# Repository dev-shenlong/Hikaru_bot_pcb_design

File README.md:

# Hikaru_bot_pcb_design
This is a repo consisting of KiCAD design files for the autonomous Differential Drive Robot

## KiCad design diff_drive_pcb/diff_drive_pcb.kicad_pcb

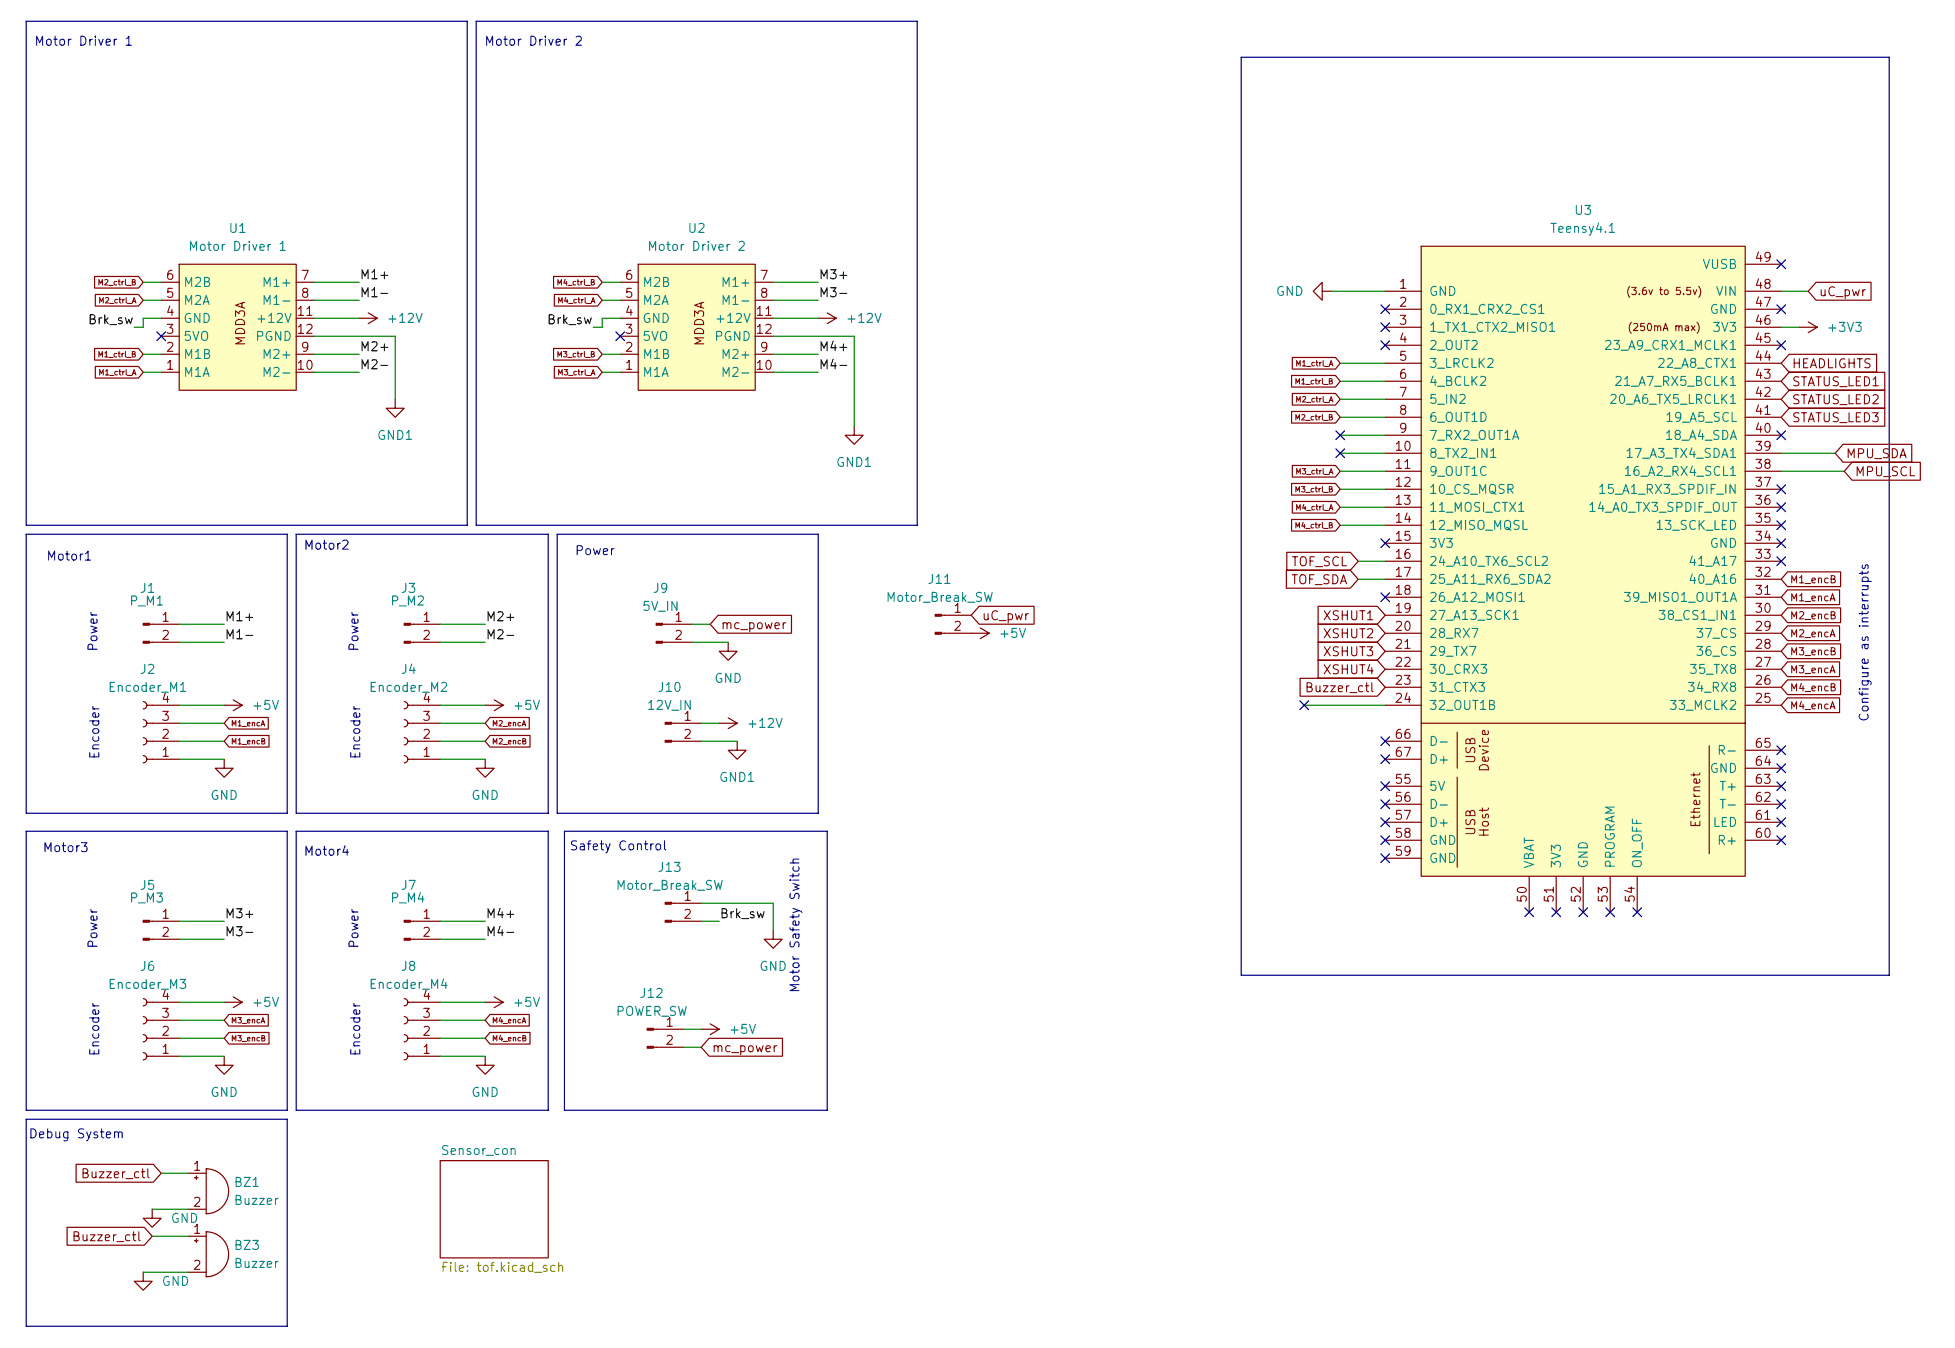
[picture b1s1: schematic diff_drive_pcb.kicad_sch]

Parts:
BZ1, BZ3: Buzzer; Buzzer_TDK_PS1240P02BT_D12.2mm_H6.5mm
J1: P_M1; JST_XH_B2B-XH-A_1x02_P2.50mm_Vertical
J2: Encoder_M1; JST_XH_B4B-XH-A_1x04_P2.50mm_Vertical
J3: P_M2; JST_XH_B2B-XH-A_1x02_P2.50mm_Vertical
J4: Encoder_M2; JST_XH_B4B-XH-A_1x04_P2.50mm_Vertical
J5: P_M3; JST_XH_B2B-XH-A_1x02_P2.50mm_Vertical
J6: Encoder_M3; JST_XH_B4B-XH-A_1x04_P2.50mm_Vertical
J7: P_M4; JST_XH_B2B-XH-A_1x02_P2.50mm_Vertical
J8: Encoder_M4; JST_XH_B4B-XH-A_1x04_P2.50mm_Vertical
J9: 5V_IN; JST_XH_B2B-XH-A_1x02_P2.50mm_Vertical
J10: 12V_IN; JST_XH_B2B-XH-A_1x02_P2.50mm_Vertical
J11, J13: Motor_Break_SW; PinHeader_1x02_P2.54mm_Vertical
J12: POWER_SW; JST_XH_B2B-XH-A_1x02_P2.50mm_Vertical
U1: Motor Driver 1; MDD3A
U2: Motor Driver 2; MDD3A
U3: Teensy4.1; Teensy41

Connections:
+3V3: U3.46 (3V3)
+5V: J2.4, J4.4, J6.4, J8.4, J11.2, J12.1; also elsewhere on the board
+12V: J10.1, U1.11 (+12V), U2.11 (+12V)
/Brk_sw: J13.2, U1.4 (GND), U2.4 (GND)
/M1+: J1.1, U1.7 (M1+)
/M1-: J1.2, U1.8 (M1-)
/M2+: J3.1, U1.9 (M2+)
/M2-: J3.2, U1.10 (M2-)
/M3+: J5.1, U2.7 (M1+)
/M3-: J5.2, U2.8 (M1-)
/M4+: J7.1, U2.9 (M2+)
/M4-: J7.2, U2.10 (M2-)
Buzzer_ctl: BZ1.1 (+), BZ3.1 (+), U3.23 (31_CTX3)
GND: BZ1.2 (-), BZ3.2 (-), J2.1, J4.1, J6.1, J8.1, J9.2, J13.1, U3.1 (GND); also elsewhere on the board
GND1: J10.2, U1.12 (PGND), U2.12 (PGND)
HEADLIGHTS: U3.44 (22_A8_CTX1); also elsewhere on the board
M1_ctrl_A: U1.1 (M1A), U3.5 (3_LRCLK2)
M1_ctrl_B: U1.2 (M1B), U3.6 (4_BCLK2)
M1_encA: J2.3, U3.31 (39_MISO1_OUT1A)
M1_encB: J2.2, U3.32 (40_A16)
M2_ctrl_A: U1.5 (M2A), U3.7 (5_IN2)
M2_ctrl_B: U1.6 (M2B), U3.8 (6_OUT1D)
M2_encA: J4.3, U3.29 (37_CS)
M2_encB: J4.2, U3.30 (38_CS1_IN1)
M3_ctrl_A: U2.1 (M1A), U3.11 (9_OUT1C)
M3_ctrl_B: U2.2 (M1B), U3.12 (10_CS_MQSR)
M3_encA: J6.3, U3.27 (35_TX8)
M3_encB: J6.2, U3.28 (36_CS)
M4_ctrl_A: U2.5 (M2A), U3.13 (11_MOSI_CTX1)
M4_ctrl_B: U2.6 (M2B), U3.14 (12_MISO_MQSL)
M4_encA: J8.3, U3.25 (33_MCLK2)
M4_encB: J8.2, U3.26 (34_RX8)
MPU_SCL: U3.38 (16_A2_RX4_SCL1); also elsewhere on the board
MPU_SDA: U3.39 (17_A3_TX4_SDA1); also elsewhere on the board
STATUS_LED1: U3.43 (21_A7_RX5_BCLK1); also elsewhere on the board
STATUS_LED2: U3.42 (20_A6_TX5_LRCLK1); also elsewhere on the board
STATUS_LED3: U3.41 (19_A5_SCL); also elsewhere on the board
TOF_SCL: U3.16 (24_A10_TX6_SCL2); also elsewhere on the board
TOF_SDA: U3.17 (25_A11_RX6_SDA2); also elsewhere on the board
XSHUT1: U3.19 (27_A13_SCK1); also elsewhere on the board
XSHUT2: U3.20 (28_RX7); also elsewhere on the board
XSHUT3: U3.21 (29_TX7); also elsewhere on the board
XSHUT4: U3.22 (30_CRX3); also elsewhere on the board
mc_power: J9.1, J12.2
uC_pwr: J11.1, U3.48 (VIN)

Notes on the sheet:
Encoder
Configure as interrupts
Motor Driver 2
Safety Control
Motor Driver 1
Motor4
Power
Motor3
Debug System
Motor2
Motor1
Motor Safety Switch

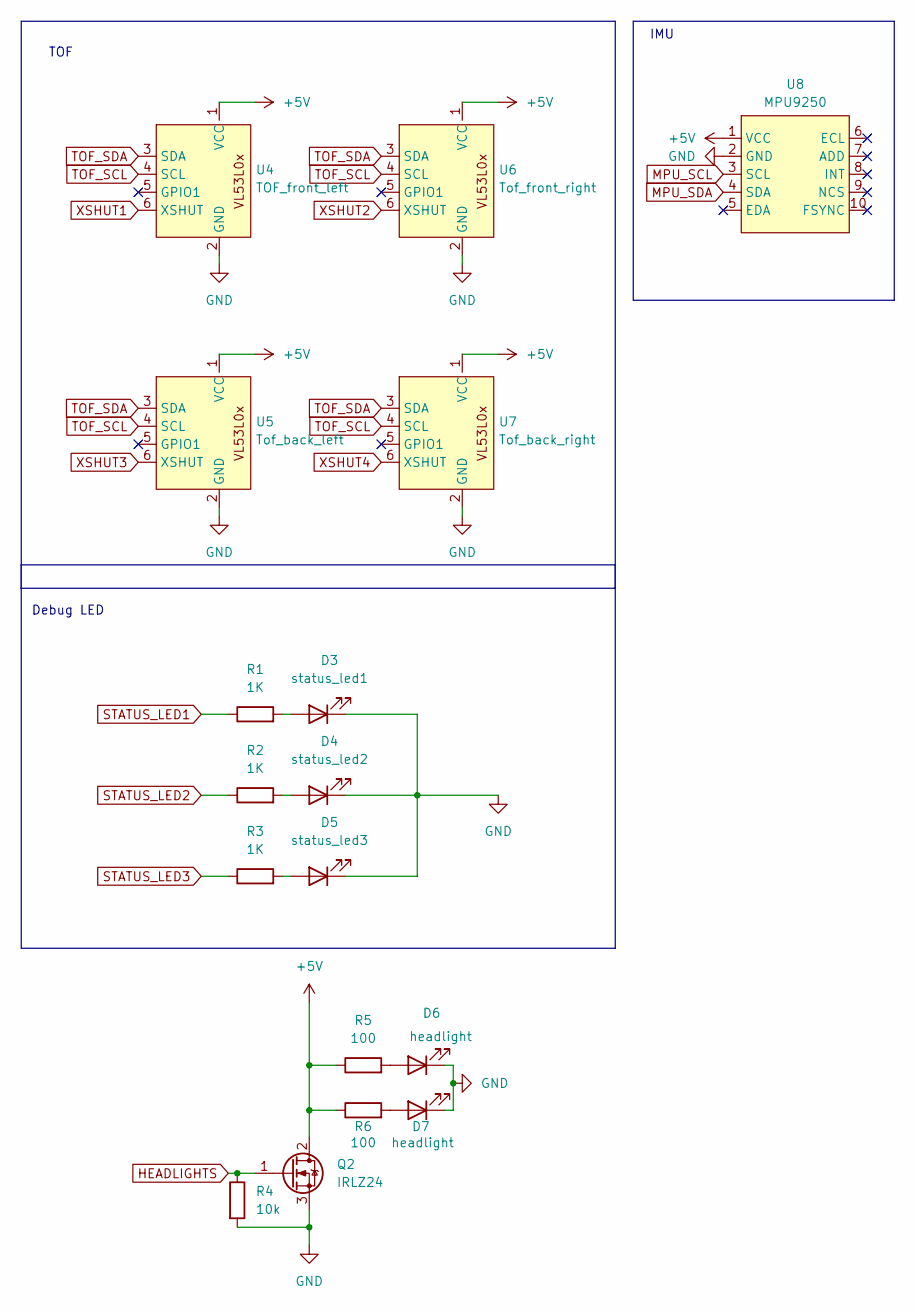
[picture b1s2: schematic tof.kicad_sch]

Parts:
D3: status_led1; PinHeader_1x02_P2.54mm_Vertical
D4: status_led2; PinHeader_1x02_P2.54mm_Vertical
D5: status_led3; PinHeader_1x02_P2.54mm_Vertical
D6, D7: headlight; PinHeader_1x02_P2.54mm_Vertical
Q2: IRLZ24; TO-220-3_Vertical
R1, R2, R3: 1K; R_Axial_DIN0204_L3.6mm_D1.6mm_P2.54mm_Vertical
R4: 10k; R_Axial_DIN0204_L3.6mm_D1.6mm_P5.08mm_Horizontal
R5, R6: 100; R_Axial_DIN0204_L3.6mm_D1.6mm_P5.08mm_Horizontal
U4: TOF_front_left; JST_XH_B6B-XH-A_1x06_P2.50mm_Vertical
U5: Tof_back_left; JST_XH_B6B-XH-A_1x06_P2.50mm_Vertical
U6: Tof_front_right; JST_XH_B6B-XH-A_1x06_P2.50mm_Vertical
U7: Tof_back_right; JST_XH_B6B-XH-A_1x06_P2.50mm_Vertical
U8: MPU9250; PinHeader_1x10_P2.54mm_Vertical

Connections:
+5V: Q2.2 (D), R5.1, R6.1, U4.1 (VCC), U5.1 (VCC), U6.1 (VCC), U7.1 (VCC), U8.1 (VCC); also elsewhere on the board
GND: D3.1 (K), D4.1 (K), D5.1 (K), D6.1 (K), D7.1 (K), Q2.3 (S), R4.2, U4.2 (GND), U5.2 (GND), U6.2 (GND), U7.2 (GND), U8.2 (GND); also elsewhere on the board
HEADLIGHTS: Q2.1 (G), R4.1; also elsewhere on the board
MPU_SCL: U8.3 (SCL); also elsewhere on the board
MPU_SDA: U8.4 (SDA); also elsewhere on the board
unnamed: D3.2 (A), R1.2
unnamed: D4.2 (A), R2.2
unnamed: D5.2 (A), R3.2
unnamed: D6.2 (A), R5.2
unnamed: D7.2 (A), R6.2
STATUS_LED1: R1.1; also elsewhere on the board
STATUS_LED2: R2.1; also elsewhere on the board
STATUS_LED3: R3.1; also elsewhere on the board
TOF_SCL: U4.4 (SCL), U5.4 (SCL), U6.4 (SCL), U7.4 (SCL); also elsewhere on the board
TOF_SDA: U4.3 (SDA), U5.3 (SDA), U6.3 (SDA), U7.3 (SDA); also elsewhere on the board
XSHUT1: U4.6 (XSHUT); also elsewhere on the board
XSHUT2: U6.6 (XSHUT); also elsewhere on the board
XSHUT3: U5.6 (XSHUT); also elsewhere on the board
XSHUT4: U7.6 (XSHUT); also elsewhere on the board

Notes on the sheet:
IMU
Debug LED
TOF

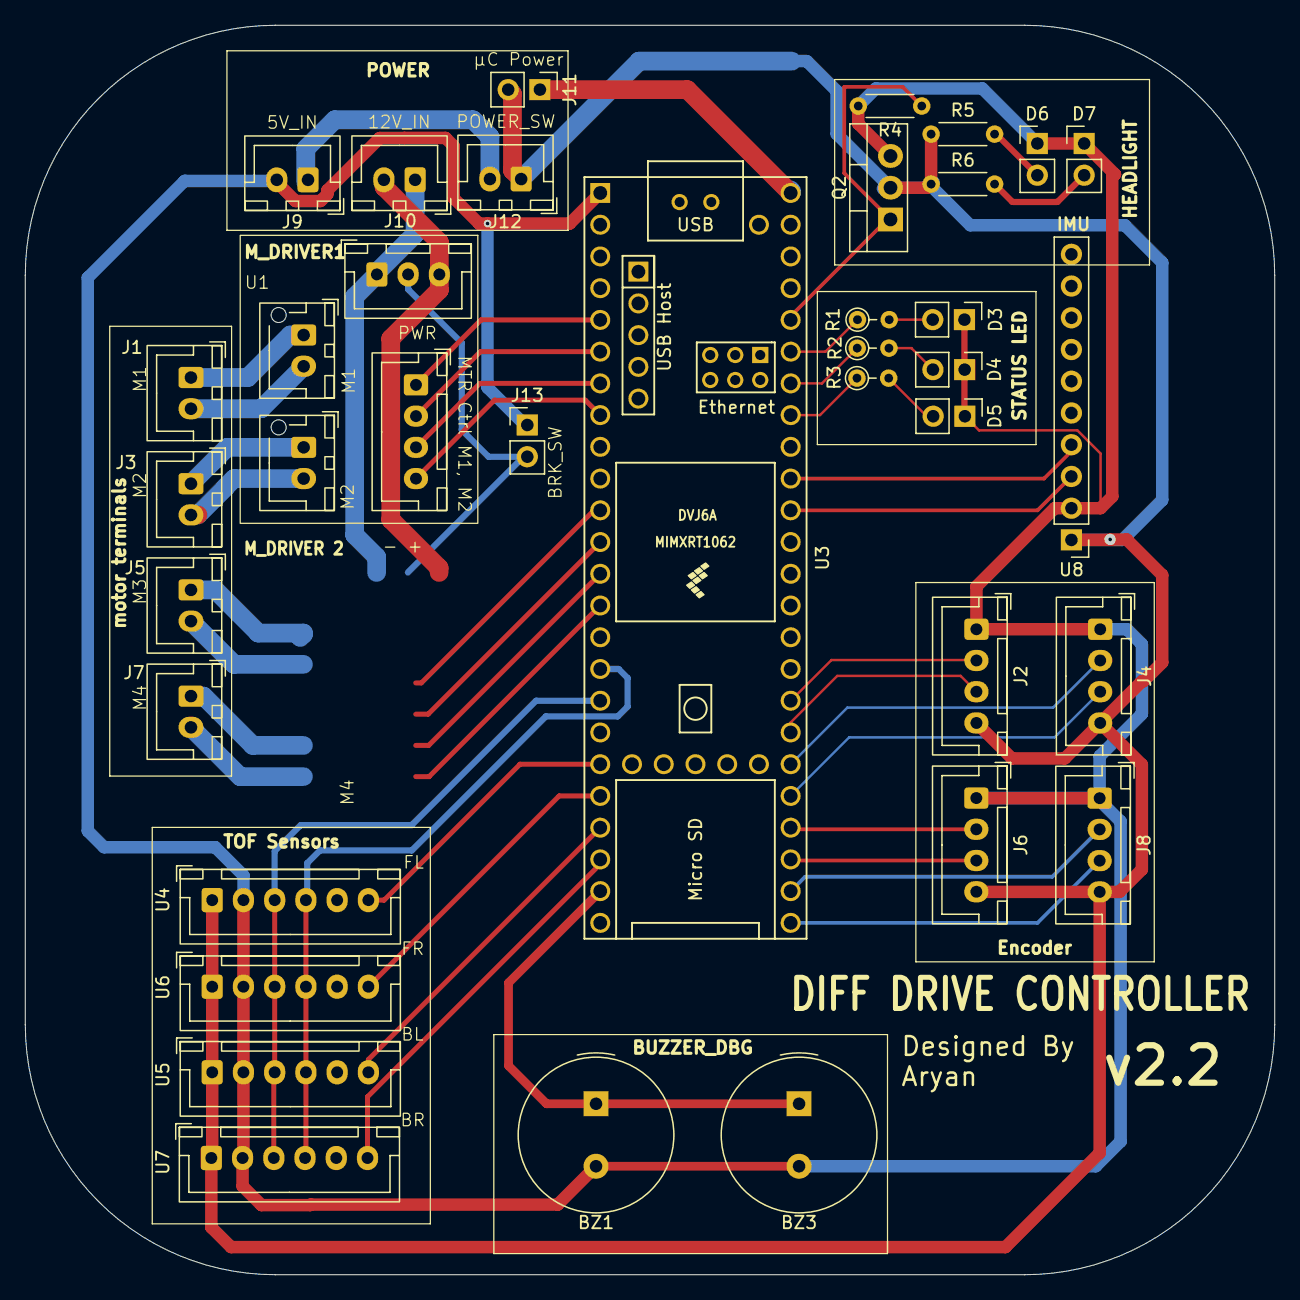
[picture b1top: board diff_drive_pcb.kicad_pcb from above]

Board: 2 copper layers, 100.0 x 100.0 mm, 34 parts (0 on the bottom side), 41 nets.

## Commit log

2025-08-27 Edited Schematic
2025-08-29 Added sensors and command signals to schematic
2025-09-02 PCB v1.0 developed
2026-02-24 Updated Schematic
2026-02-24 Rev 2.1 pcb design
2026-02-24 Cleaned up PCB and adjusted size
2026-02-24 Isolated 12V GND from uC GND
2026-02-24 V2.2 changes to power system
2026-02-24 Generated gerb files for v2.2
